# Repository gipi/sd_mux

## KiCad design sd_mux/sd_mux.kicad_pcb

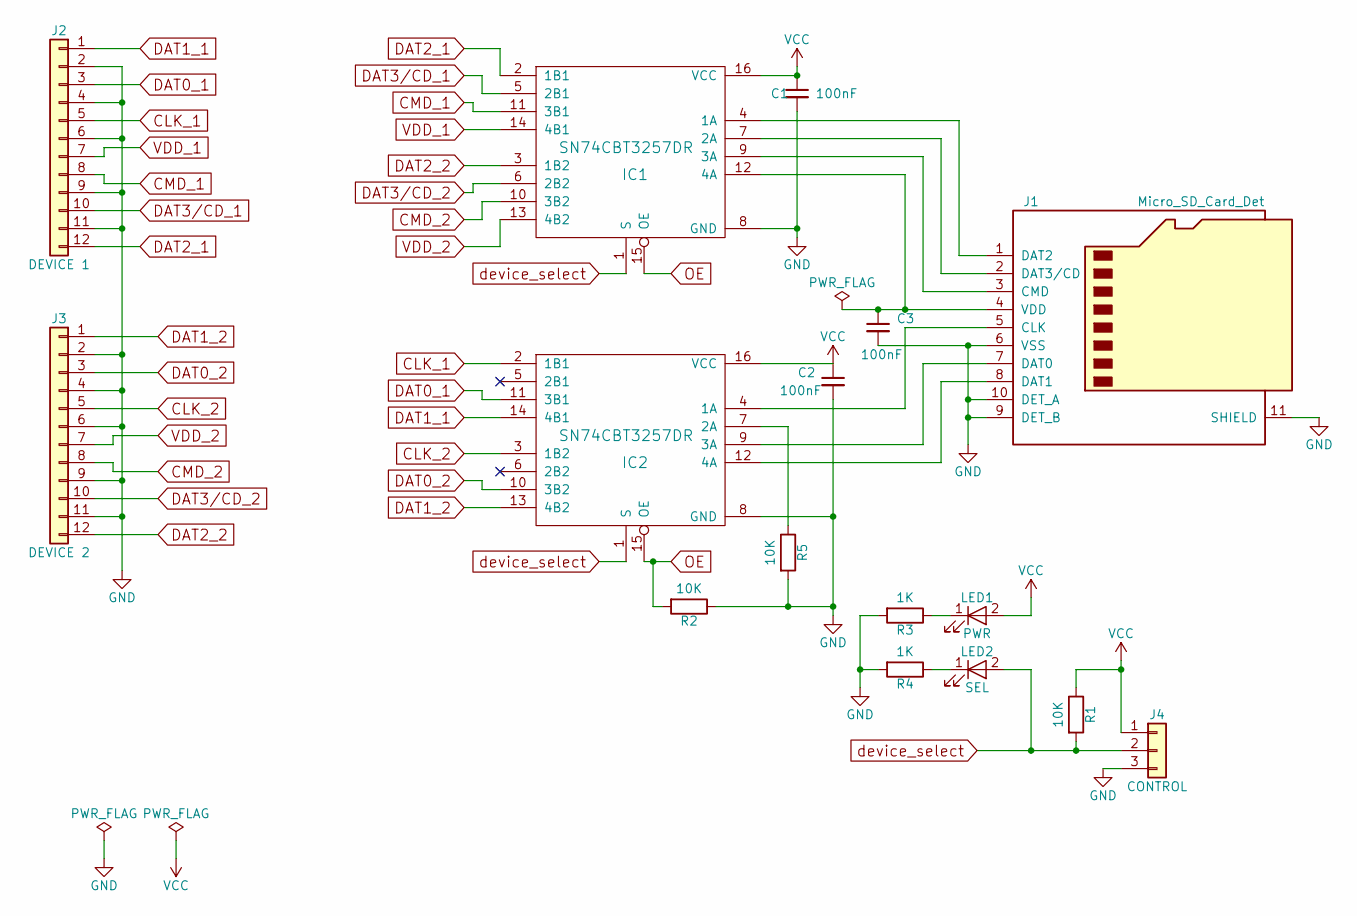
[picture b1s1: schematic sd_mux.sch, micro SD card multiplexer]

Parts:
C1, C2, C3: 100nF; C_0603_HandSoldering
IC1, IC2: SN74CBT3257DR; SO-16-N
J1: Micro_SD_Card_Det; push_pull_uSD_slot_1040310811
J2: DEVICE 1; FFC_connector_SFW12R-2STE1LF
J3: DEVICE 2; FFC_connector_SFW12R-2STE1LF
J4: CONTROL; Pin_Header_Straight_1x03_Pitch2.54mm
LED1: PWR; LED_0603_HandSoldering
LED2: SEL; LED_0603_HandSoldering
R1, R2, R5: 10K; R_0603_HandSoldering
R3, R4: 1K; R_0603_HandSoldering

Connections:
CLK_1: IC2.2 (1B1), J2.5
CLK_2: IC2.3 (1B2), J3.5
CMD: IC1.9 (3A), J1.3 (CMD); also elsewhere on the board
CMD_1: IC1.11 (3B1), J2.8
CMD_2: IC1.10 (3B2), J3.8
DAT0_1: IC2.11 (3B1), J2.3
DAT0_2: IC2.10 (3B2), J3.3
DAT1_1: IC2.14 (4B1), J2.1
DAT1_2: IC2.13 (4B2), J3.1
DAT2_1: IC1.2 (1B1), J2.12
DAT2_2: IC1.3 (1B2), J3.12
DAT3/CD: IC1.7 (2A), J1.2 (DAT3/CD); also elsewhere on the board
DAT3/CD_1: IC1.5 (2B1), J2.10
DAT3/CD_2: IC1.6 (2B2), J3.10
GND: C1.2, C2.2, C3.2, IC1.8 (GND), IC2.8 (GND), J1.6 (VSS), J1.9 (DET_B), J1.10 (DET_A), J1.11 (SHIELD), J2.2, J2.4, J2.6, J2.9, J2.11, J3.2, J3.4, J3.6, J3.9, J3.11, J4.3, R2.1, R3.2, R4.2, R5.2; also elsewhere on the board
unnamed: IC1.4 (1A), J1.1 (DAT2)
unnamed: IC2.4 (1A), J1.5 (CLK)
unnamed: IC2.7 (2A), R5.1
unnamed: IC2.9 (3A), J1.7 (DAT0)
unnamed: IC2.12 (4A), J1.8 (DAT1)
unnamed: LED1.1 (K), R3.1
unnamed: LED2.1 (K), R4.1
OE: IC1.15 (OE), IC2.15 (OE), R2.2
VDD: C3.1, IC1.12 (4A), J1.4 (VDD); also elsewhere on the board
VDD_1: IC1.14 (4B1), J2.7
VDD_2: IC1.13 (4B2), J3.7
device_select: IC1.1 (S), IC2.1 (S), J4.2, LED2.2 (A), R1.2

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
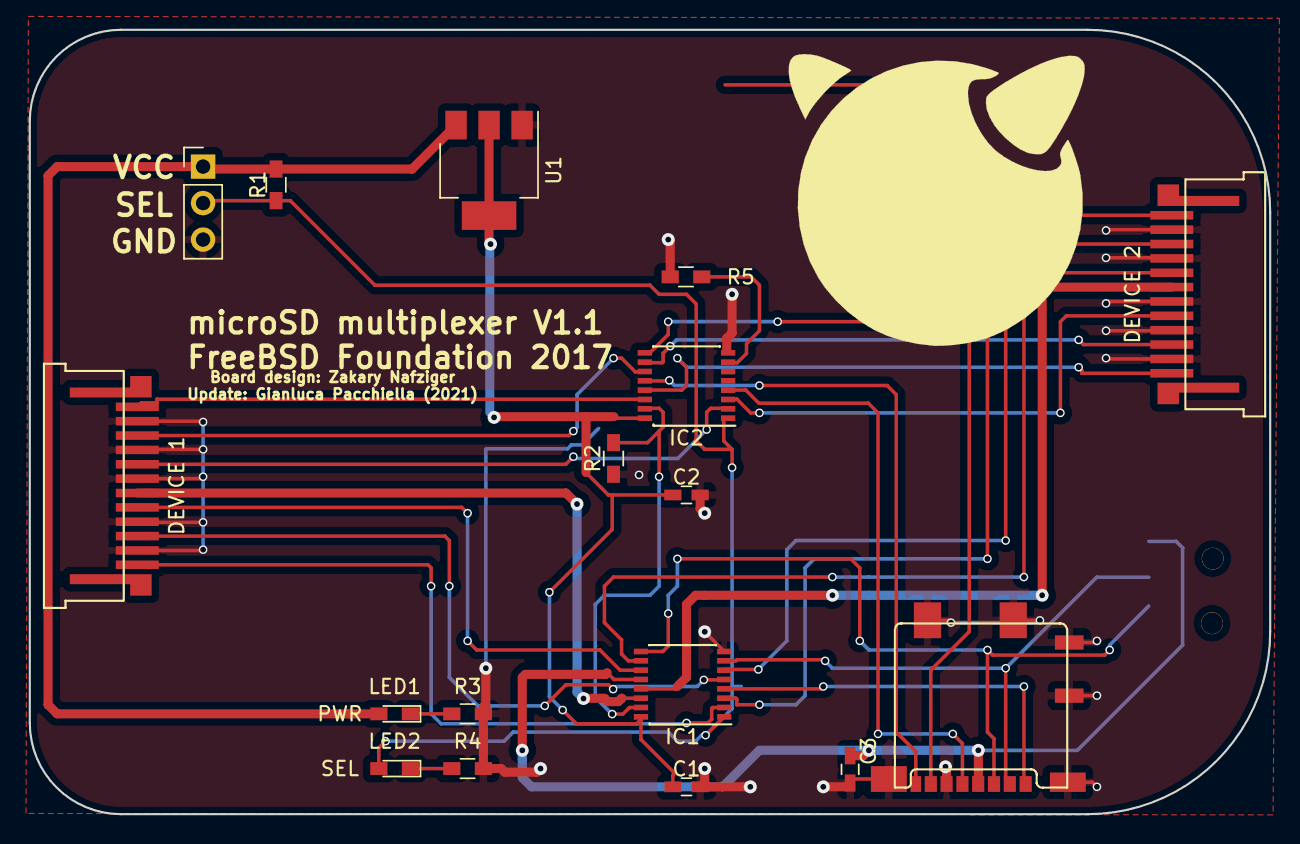
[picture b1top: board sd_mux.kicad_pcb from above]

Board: 2 copper layers, 86.4 x 54.6 mm, 18 parts (1 on the bottom side), 29 nets.

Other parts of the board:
J5: USB_A; USB aliexpress
U1: AMS1117-3.3; SOT-223-3_TabPin2

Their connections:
CMD: J5.3 (D+); also elsewhere on the board
DAT3/CD: J5.2 (D-); also elsewhere on the board
GND: J5.4 (GND), U1.1 (GND); also elsewhere on the board
VDD: J5.1 (VBUS); also elsewhere on the board

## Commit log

2022-05-26 Use the SN74CB3Q3257.
